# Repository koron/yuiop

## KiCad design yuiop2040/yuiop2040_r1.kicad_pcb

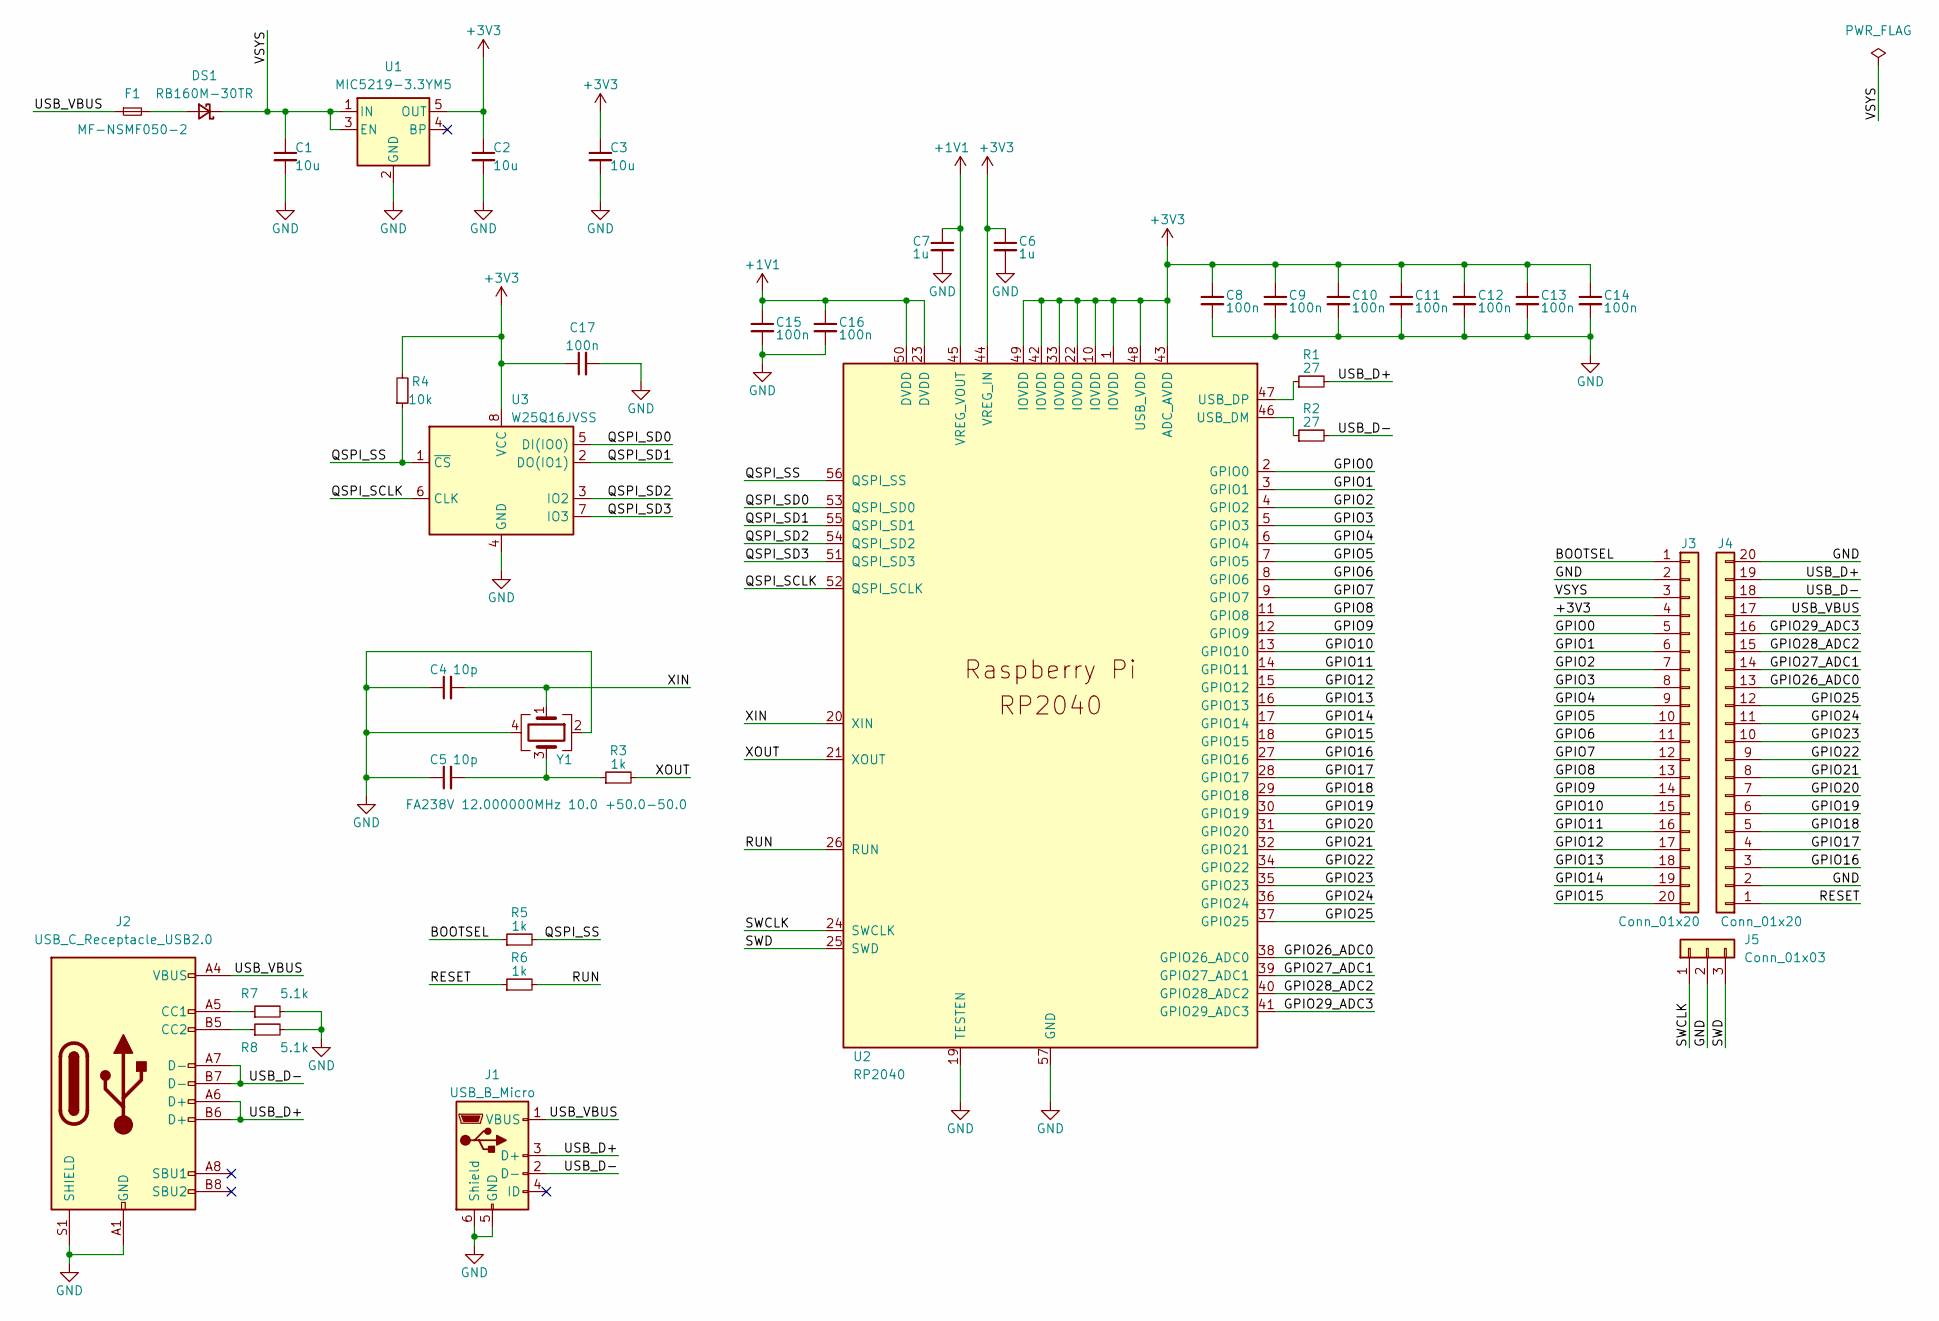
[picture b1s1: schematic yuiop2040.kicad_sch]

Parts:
C1, C2, C3: 10u; C_0603_1608Metric
C4, C5: 10p; C_0603_1608Metric
C6, C7: 1u; C_0603_1608Metric
C8, C9, C10, C11, C12, C13, C14, C15, C16, C17: 100n; C_0603_1608Metric
DS1: RB160M-30TR; D_SOD-123
F1: MF-NSMF050-2; Fuse_1206_3216Metric
J1: USB_B_Micro; USB_Micro-B_Amphenol_10103594-0001LF_Horizontal
J2: USB_C_Receptacle_USB2.0; USB_C_Receptacle_XKB_U262-16XN-4BVC11
J3, J4: Conn_01x20; PinHeader_1x20_P2.54mm_Vertical
J5: Conn_01x03; PinHeader_1x03_P2.54mm_Vertical
R1, R2: 27; R_0603_1608Metric
R3, R5, R6: 1k; R_0603_1608Metric
R4: 10k; R_0603_1608Metric
R7, R8: 5.1k; R_0603_1608Metric
U1: MIC5219-3.3YM5; SOT-23-5
U2: RP2040; RP2040-QFN-56-r2
U3: W25Q16JVSS; SOIC-8_3.9x4.9mm_P1.27mm
Y1: FA238V 12.000000MHz 10.0 +50.0-50.0; Crystal_SMD_SeikoEpson_FA238V-4Pin_3.2x2.5mm

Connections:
+1V1: C7.1, C15.1, C16.1, U2.23 (DVDD), U2.45 (VREG_VOUT), U2.50 (DVDD)
+3V3: C2.1, C3.1, C6.1, C8.1, C9.1, C10.1, C11.1, C12.1, C13.1, C14.1, C17.1, J3.4, R4.2, U1.5 (OUT), U2.1 (IOVDD), U2.10 (IOVDD), U2.22 (IOVDD), U2.33 (IOVDD), U2.42 (IOVDD), U2.43 (ADC_AVDD), U2.44 (VREG_IN), U2.48 (USB_VDD), U2.49 (IOVDD), U3.8 (VCC)
/BOOTSEL: J3.1, R5.1
/GPIO0: J3.5, U2.2 (GPIO0)
/GPIO1: J3.6, U2.3 (GPIO1)
/GPIO2: J3.7, U2.4 (GPIO2)
/GPIO3: J3.8, U2.5 (GPIO3)
/GPIO4: J3.9, U2.6 (GPIO4)
/GPIO5: J3.10, U2.7 (GPIO5)
/GPIO6: J3.11, U2.8 (GPIO6)
/GPIO7: J3.12, U2.9 (GPIO7)
/GPIO8: J3.13, U2.11 (GPIO8)
/GPIO9: J3.14, U2.12 (GPIO9)
/GPIO10: J3.15, U2.13 (GPIO10)
/GPIO11: J3.16, U2.14 (GPIO11)
/GPIO12: J3.17, U2.15 (GPIO12)
/GPIO13: J3.18, U2.16 (GPIO13)
/GPIO14: J3.19, U2.17 (GPIO14)
/GPIO15: J3.20, U2.18 (GPIO15)
/GPIO16: J4.3, U2.27 (GPIO16)
/GPIO17: J4.4, U2.28 (GPIO17)
/GPIO18: J4.5, U2.29 (GPIO18)
/GPIO19: J4.6, U2.30 (GPIO19)
/GPIO20: J4.7, U2.31 (GPIO20)
/GPIO21: J4.8, U2.32 (GPIO21)
/GPIO22: J4.9, U2.34 (GPIO22)
/GPIO23: J4.10, U2.35 (GPIO23)
/GPIO24: J4.11, U2.36 (GPIO24)
/GPIO25: J4.12, U2.37 (GPIO25)
/GPIO26_ADC0: J4.13, U2.38 (GPIO26_ADC0)
/GPIO27_ADC1: J4.14, U2.39 (GPIO27_ADC1)
/GPIO28_ADC2: J4.15, U2.40 (GPIO28_ADC2)
/GPIO29_ADC3: J4.16, U2.41 (GPIO29_ADC3)
/QSPI_SCLK: U2.52 (QSPI_SCLK), U3.6 (CLK)
/QSPI_SD0: U2.53 (QSPI_SD0), U3.5 (DI(IO0))
/QSPI_SD1: U2.55 (QSPI_SD1), U3.2 (DO(IO1))
/QSPI_SD2: U2.54 (QSPI_SD2), U3.3 (IO2)
/QSPI_SD3: U2.51 (QSPI_SD3), U3.7 (IO3)
/QSPI_SS: R4.1, R5.2, U2.56 (QSPI_SS), U3.1 (~CS)
/RESET: J4.1, R6.1
/RUN: R6.2, U2.26 (RUN)
/SWCLK: J5.1, U2.24 (SWCLK)
/SWD: J5.3, U2.25 (SWD)
/USB_D+: J1.3 (D+), J2.A6 (D+), J2.B6 (D+), J4.19, R1.2
/USB_D-: J1.2 (D-), J2.A7 (D-), J2.B7 (D-), J4.18, R2.2
/USB_VBUS: F1.1, J1.1 (VBUS), J2.A4 (VBUS), J2.A9 (VBUS), J2.B4 (VBUS), J2.B9 (VBUS), J4.17
/VSYS: C1.1, DS1.1 (K), J3.3, U1.1 (IN), U1.3 (EN)
/XIN: C4.2, U2.20 (XIN), Y1.1
/XOUT: R3.2, U2.21 (XOUT)
GND: C1.2, C2.2, C3.2, C4.1, C5.1, C6.2, C7.2, C8.2, C9.2, C10.2, C11.2, C12.2, C13.2, C14.2, C15.2, C16.2, C17.2, J1.5 (GND), J1.6 (Shield), J2.A1 (GND), J2.A12 (GND), J2.B1 (GND), J2.B12 (GND), J2.S1 (SHIELD), J3.2, J4.2, J4.20, J5.2, R7.2, R8.2, U1.2 (GND), U2.19 (TESTEN), U2.57 (GND), U3.4 (GND), Y1.2, Y1.4; also elsewhere on the board
unnamed: C5.2, R3.1, Y1.3
unnamed: DS1.2 (A), F1.2
unnamed 52: J2.A5 (CC1), R7.1; also elsewhere on the board
unnamed 53: J2.B5 (CC2), R8.1; also elsewhere on the board
unnamed: R1.1, U2.47 (USB_DP)
unnamed: R2.1, U2.46 (USB_DM)

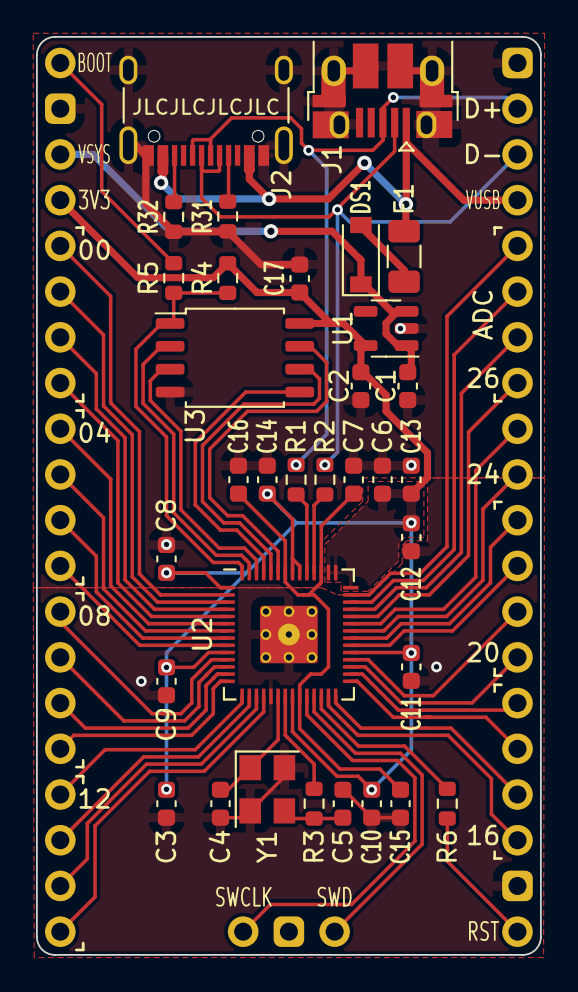
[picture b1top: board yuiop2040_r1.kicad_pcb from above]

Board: 2 copper layers, 28.0 x 51.0 mm, 36 parts (0 on the bottom side), 56 nets.

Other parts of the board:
R31, R32: 5.1k; R_0603_1608Metric

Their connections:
GND: R31.2, R32.2; also elsewhere on the board
unnamed 52: R31.1; also elsewhere on the board
unnamed 53: R32.1; also elsewhere on the board

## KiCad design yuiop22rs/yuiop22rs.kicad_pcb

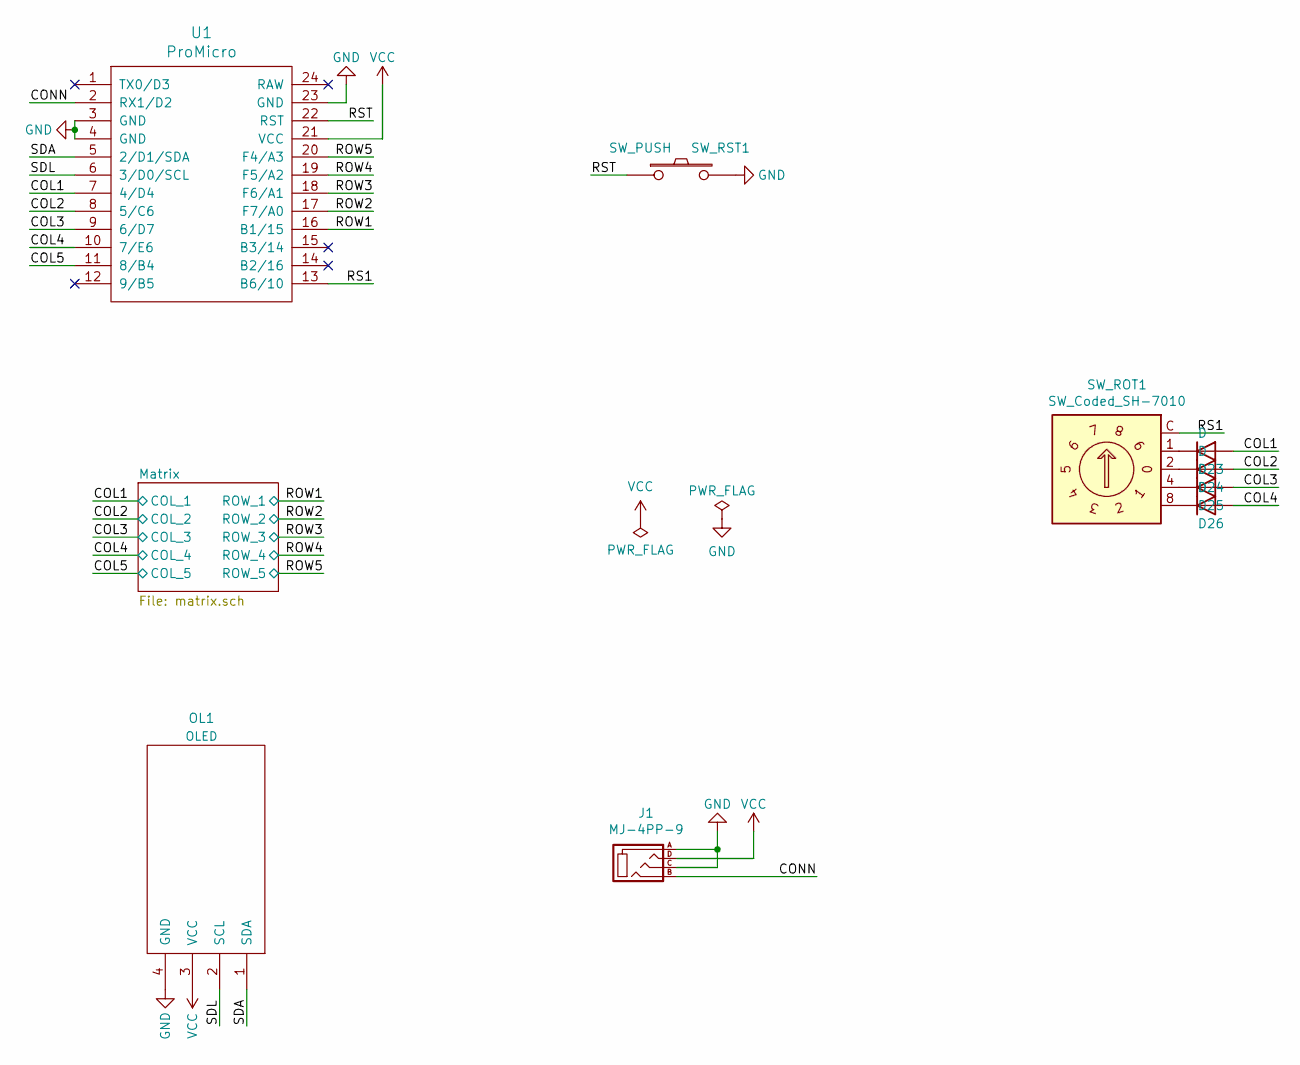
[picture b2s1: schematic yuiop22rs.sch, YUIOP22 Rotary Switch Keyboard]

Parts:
D23, D24, D25, D26: D; D3_SMD_v2_B
J1: MJ-4PP-9; MJ-4PP-9_1side
OL1: OLED; OLED_128x32
SW_ROT1: SW_Coded_SH-7010; Nidec_Copal_SH-7010C
SW_RST1: SW_PUSH; ResetSW_2_1side
U1: ProMicro; ProMicro_v3

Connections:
/COL1: D23.2 (A), U1.7 (4/D4); also elsewhere on the board
/COL2: D24.2 (A), U1.8 (5/C6); also elsewhere on the board
/COL3: D25.2 (A), U1.9 (6/D7); also elsewhere on the board
/COL4: D26.2 (A), U1.10 (7/E6); also elsewhere on the board
/COL5: U1.11 (8/B4); also elsewhere on the board
/CONN: J1.B, U1.2 (RX1/D2)
/ROW1: U1.16 (B1/15); also elsewhere on the board
/ROW2: U1.17 (F7/A0); also elsewhere on the board
/ROW3: U1.18 (F6/A1); also elsewhere on the board
/ROW4: U1.19 (F5/A2); also elsewhere on the board
/ROW5: U1.20 (F4/A3); also elsewhere on the board
/RS1: SW_ROT1.C, U1.13 (B6/10)
/RST: SW_RST1.1, U1.22 (RST)
/SDA: OL1.1 (SDA), U1.5 (2/D1/SDA)
/SDL: OL1.2 (SCL), U1.6 (3/D0/SCL)
GND: J1.A, J1.C, OL1.4 (GND), SW_RST1.2, U1.3 (GND), U1.4 (GND), U1.23 (GND)
unnamed: D23.1 (K), SW_ROT1.1
unnamed: D24.1 (K), SW_ROT1.2
unnamed: D25.1 (K), SW_ROT1.4
unnamed: D26.1 (K), SW_ROT1.8
VCC: J1.D, OL1.3 (VCC), U1.21 (VCC)

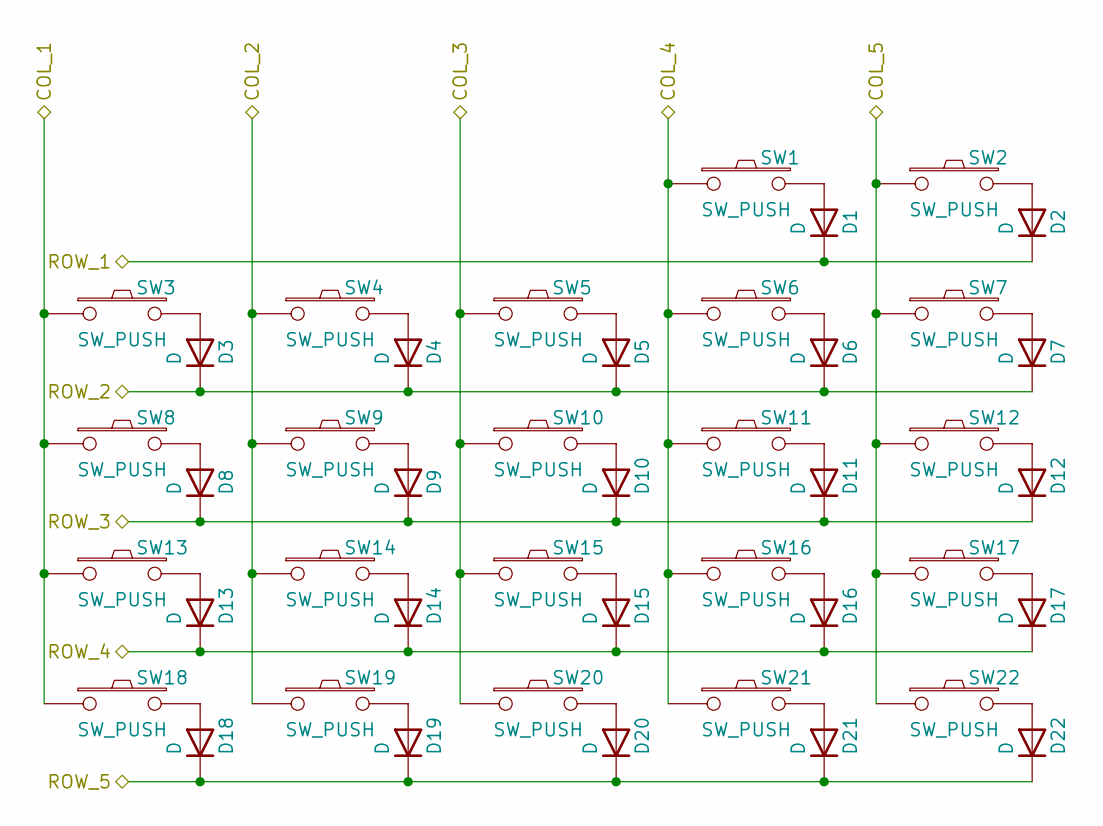
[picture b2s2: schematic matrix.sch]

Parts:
D1, D2, D3, D4, D5, D6, D7, D8, D9, D10, D11, D12, D13, D14, D15, D16, D17, D18, D19, D20, D21, D22: D; D3_SMD_v2_B
SW1, SW2, SW3, SW4, SW5, SW6, SW7, SW8, SW9, SW10, SW11, SW12, SW13, SW14, SW15, SW16, SW17, SW18, SW19, SW20, SW21, SW22: SW_PUSH; Switch_CherryMX_1.00u

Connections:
/COL1: SW3.1, SW8.1, SW13.1, SW18.1; also elsewhere on the board
/COL2: SW4.1, SW9.1, SW14.1, SW19.1; also elsewhere on the board
/COL3: SW5.1, SW10.1, SW15.1, SW20.1; also elsewhere on the board
/COL4: SW1.1, SW6.1, SW11.1, SW16.1, SW21.1; also elsewhere on the board
/COL5: SW2.1, SW7.1, SW12.1, SW17.1, SW22.1; also elsewhere on the board
/ROW1: D1.1 (K), D2.1 (K); also elsewhere on the board
/ROW2: D3.1 (K), D4.1 (K), D5.1 (K), D6.1 (K), D7.1 (K); also elsewhere on the board
/ROW3: D8.1 (K), D9.1 (K), D10.1 (K), D11.1 (K), D12.1 (K); also elsewhere on the board
/ROW4: D13.1 (K), D14.1 (K), D15.1 (K), D16.1 (K), D17.1 (K); also elsewhere on the board
/ROW5: D18.1 (K), D19.1 (K), D20.1 (K), D21.1 (K), D22.1 (K); also elsewhere on the board
unnamed: D1.2 (A), SW1.2
unnamed: D2.2 (A), SW2.2
unnamed: D3.2 (A), SW3.2
unnamed: D4.2 (A), SW4.2
unnamed: D5.2 (A), SW5.2
unnamed: D6.2 (A), SW6.2
unnamed: D7.2 (A), SW7.2
unnamed: D8.2 (A), SW8.2
unnamed: D9.2 (A), SW9.2
unnamed: D10.2 (A), SW10.2
unnamed: D11.2 (A), SW11.2
unnamed: D12.2 (A), SW12.2
unnamed: D13.2 (A), SW13.2
unnamed: D14.2 (A), SW14.2
unnamed: D15.2 (A), SW15.2
unnamed: D16.2 (A), SW16.2
unnamed: D17.2 (A), SW17.2
unnamed: D18.2 (A), SW18.2
unnamed: D19.2 (A), SW19.2
unnamed: D20.2 (A), SW20.2
unnamed: D21.2 (A), SW21.2
unnamed: D22.2 (A), SW22.2

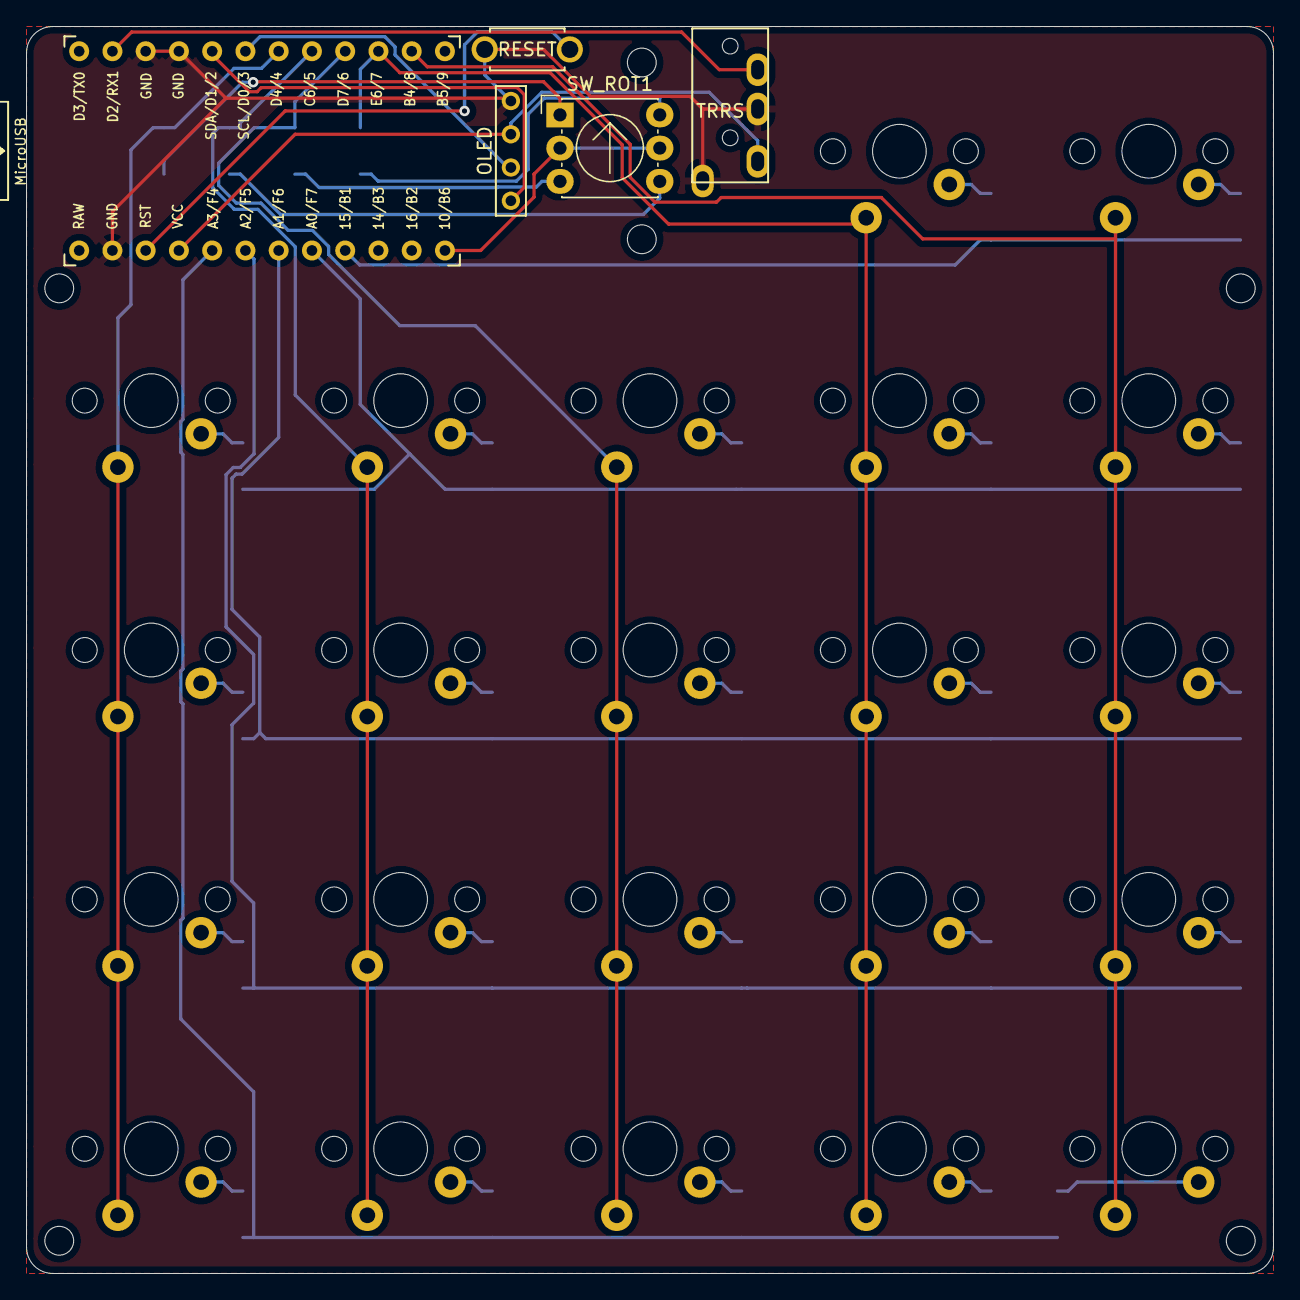
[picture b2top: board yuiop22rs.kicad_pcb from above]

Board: 2 copper layers, 95.2 x 95.2 mm, 53 parts (0 on the bottom side), 43 nets.
